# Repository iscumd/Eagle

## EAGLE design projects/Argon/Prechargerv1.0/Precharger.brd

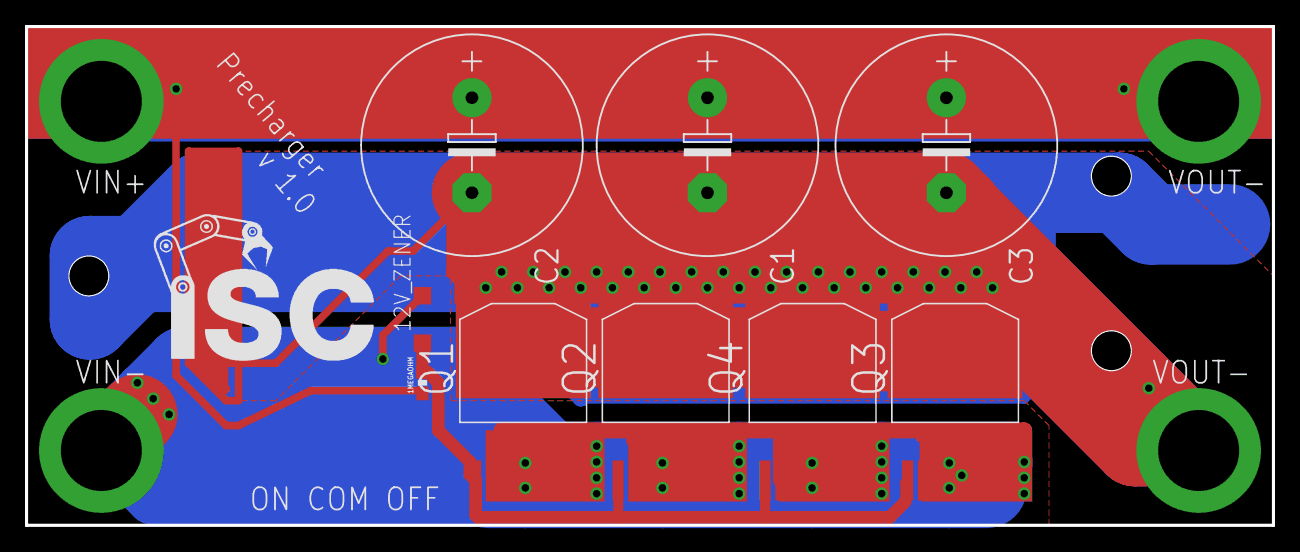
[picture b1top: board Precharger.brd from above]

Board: 2 copper layers, 100.0 x 40.0 mm, 9 parts (0 on the bottom side), 4 nets.

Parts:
1MEGAOHM: 0603-RES
12V_ZENER: SOD123
C1, C2, C3: E7,5-18
Q1, Q2, Q3, Q4: NMOSFET-D2PAK-7; D2PAK-7

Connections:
DRAIN: C1.-, C2.-, C3.-, Q1.D, Q2.D, Q3.D, Q4.D
GATE: 1MEGAOHM.2, 12V_ZENER.C, Q1.G, Q2.G, Q3.G, Q4.G
IN: C1.+, C2.+, C3.+
SOURCE: Q1.S1, Q1.S2, Q1.S3, Q1.S4, Q1.S5, Q2.S1, Q2.S2, Q2.S3, Q2.S4, Q2.S5, Q3.S1, Q3.S2, Q3.S3, Q3.S4, Q3.S5, Q4.S1, Q4.S2, Q4.S3, Q4.S4, Q4.S5

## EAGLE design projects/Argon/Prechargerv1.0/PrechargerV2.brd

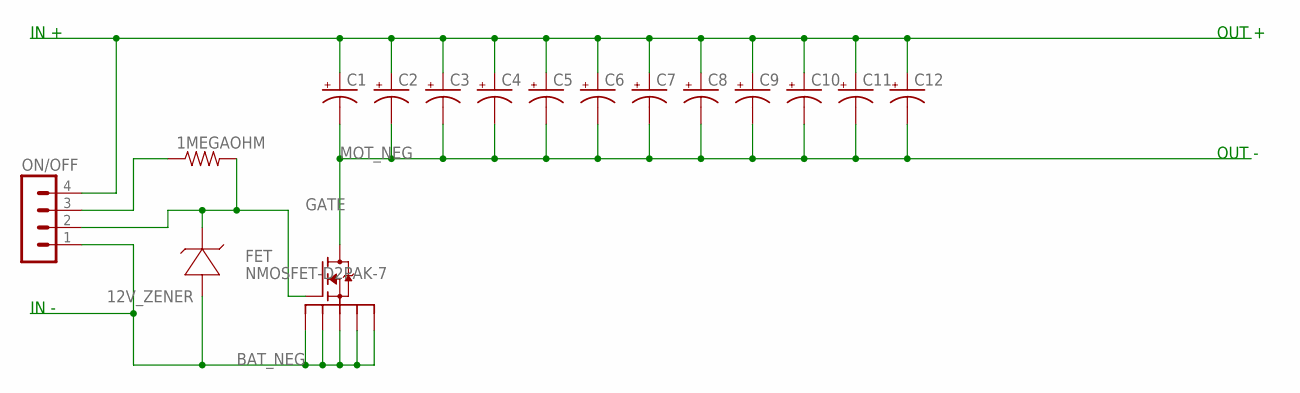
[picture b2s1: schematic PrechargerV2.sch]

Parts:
1MEGAOHM: RESISTOR0603-RES; 0603-RES
12V_ZENER: ZENER; SOD123
C1, C2, C3, C4, C5, C6, C7, C8, C9, C10, C11, C12: CPOL-USE5-13; E5-13
FET: NMOSFET-D2PAK-7; D2PAK-7
ON/OFF: MA04-1

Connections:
BAT_NEG: 12V_ZENER.A (+), FET.S1, FET.S2, FET.S3, FET.S4, FET.S5, ON/OFF.1
BAT_POS: C1.+, C2.+, C3.+, C4.+, C5.+, C6.+, C7.+, C8.+, C9.+, C10.+, C11.+, C12.+
GATE: 1MEGAOHM.2, 12V_ZENER.C (-), FET.G, ON/OFF.2
MOT_NEG: C1.-, C2.-, C3.-, C4.-, C5.-, C6.-, C7.-, C8.-, C9.-, C10.-, C11.-, C12.-, FET.D
unnamed: 1MEGAOHM.1, ON/OFF.3

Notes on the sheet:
OUT -
OUT +
IN -
IN +

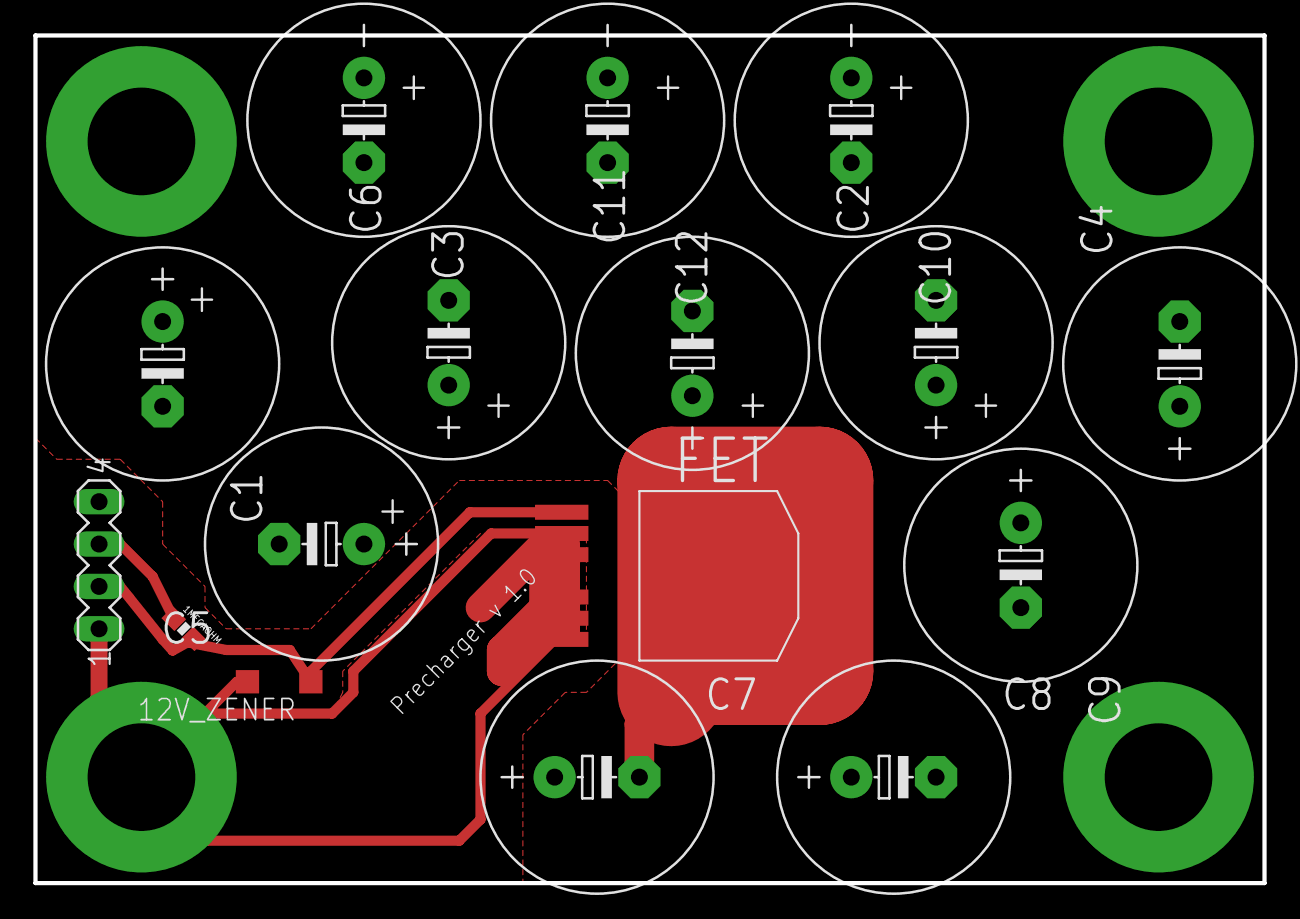
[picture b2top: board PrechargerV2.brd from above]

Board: 2 copper layers, 73.7 x 50.8 mm, 16 parts (0 on the bottom side), 5 nets.

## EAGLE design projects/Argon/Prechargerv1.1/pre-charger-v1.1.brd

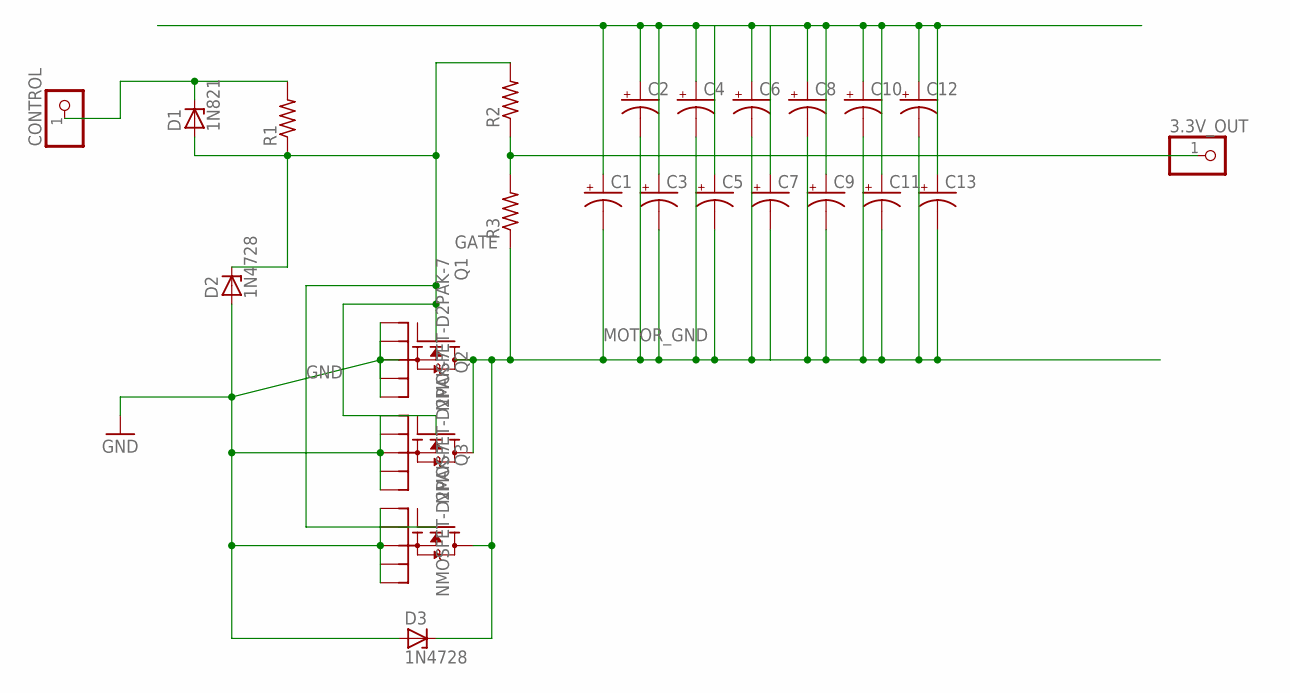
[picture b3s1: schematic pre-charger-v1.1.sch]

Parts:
3.3V_OUT: PINHD-1X1; 1X01
C1, C2, C3, C4, C5, C6, C7, C8, C9, C10, C11, C12, C13: CPOL-USE3.5-8; E3,5-8
CONTROL: PINHD-1X1; 1X01
D1: 1N821; DO35Z10
D2, D3: 1N4728; DO41Z10
Q1, Q2, Q3: NMOSFET-D2PAK-7; D2PAK-7
R1, R2, R3: R-US_0204/7; 0204/7

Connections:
3.3V_OUT: 3.3V_OUT.1, R2.1, R3.2
GATE: D1.A, D2.C, R1.1, R2.2
GND: D2.A, D3.A, Q1.S1, Q1.S2, Q1.S3, Q1.S4, Q1.S5, Q2.S1, Q2.S5, Q3.S1, Q3.S5
MOTOR_GND: C1.-, C2.-, C3.-, C4.-, C5.-, C6.-, C7.-, C8.-, C9.-, C10.-, C11.-, C12.-, C13.-, D3.C, Q1.D, Q2.D, Q3.D, R3.1
unnamed: CONTROL.1, D1.C, R1.2
V_BATT: C1.+, C2.+, C3.+, C4.+, C5.+, C6.+, C7.+, C8.+, C9.+, C10.+, C11.+, C12.+, C13.+

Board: 2 copper layers, 24 parts (0 on the bottom side), 6 nets, no tracks yet.

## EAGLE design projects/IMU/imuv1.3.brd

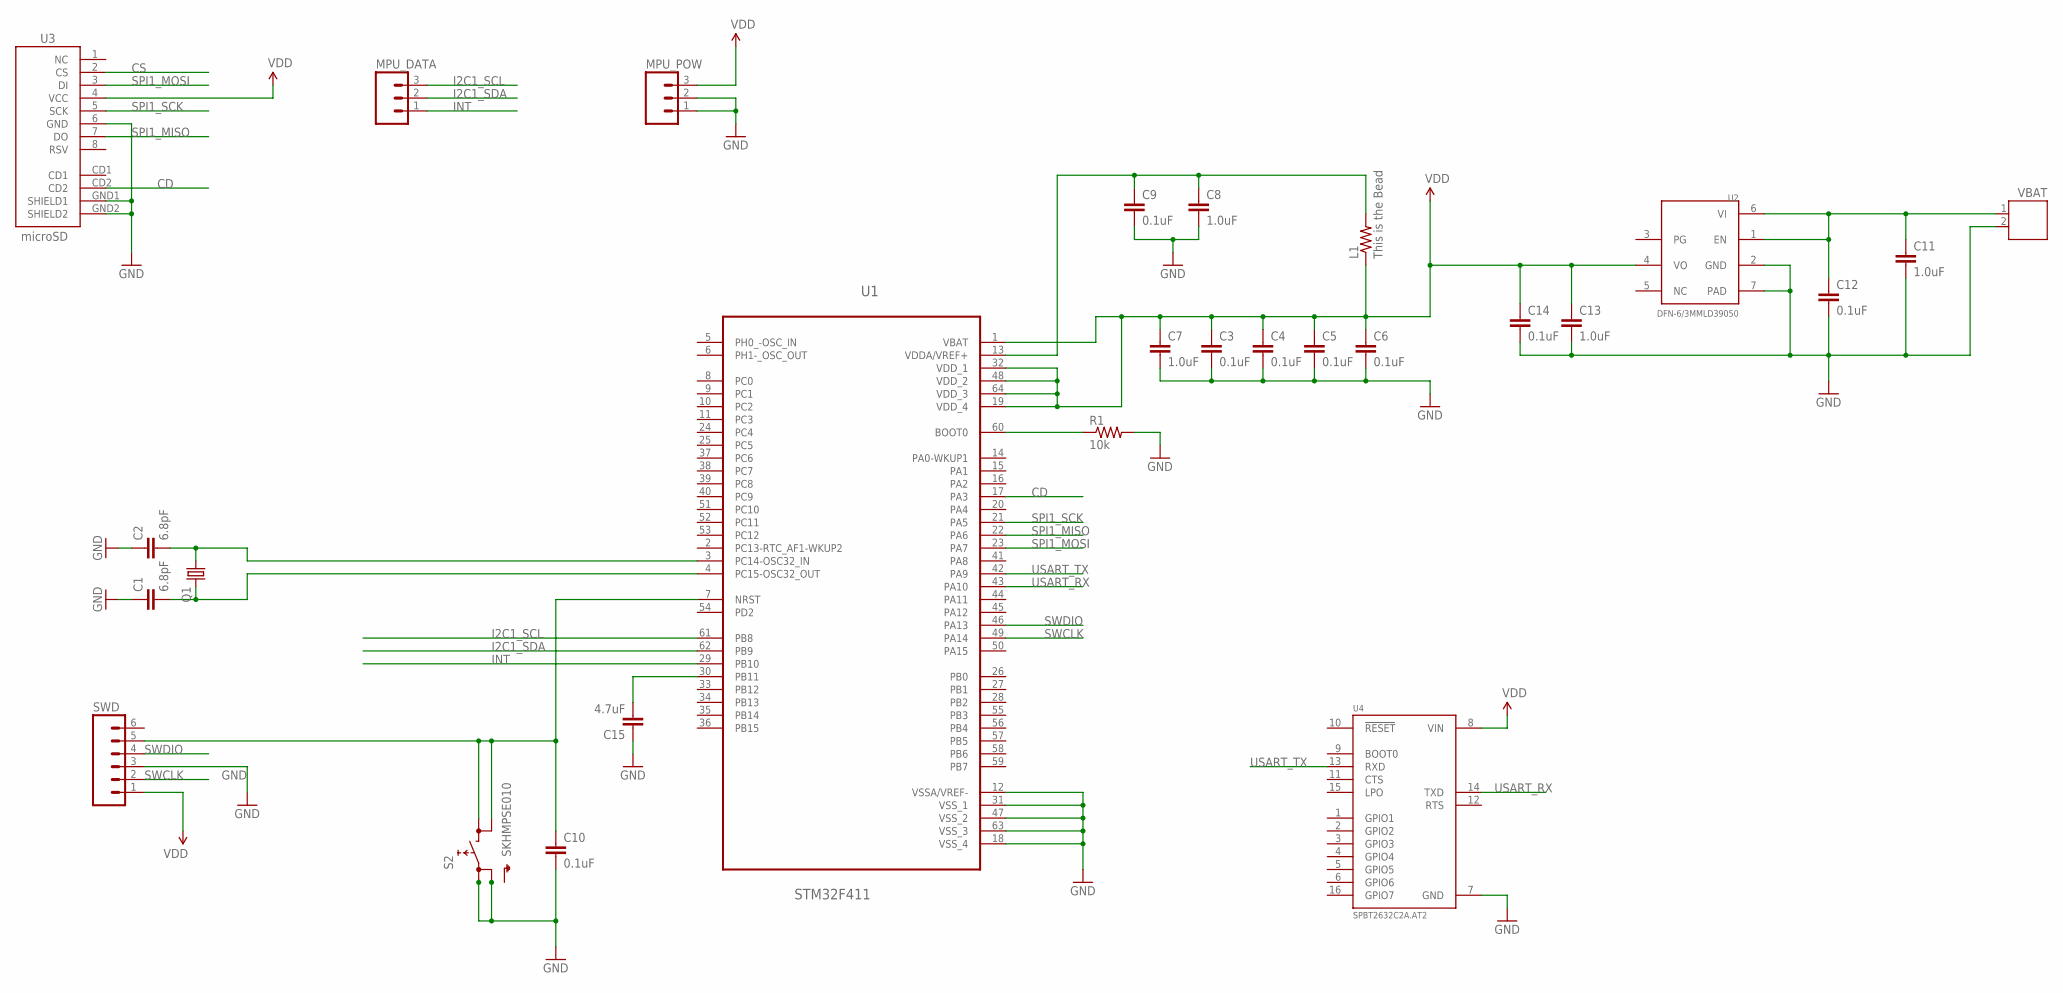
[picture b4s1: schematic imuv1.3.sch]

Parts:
C1, C2: 6.8pF; 0603-CAP
C3, C4, C5, C6, C9, C10, C12, C14: 0.1uF; 0603-CAP
C7, C8, C11, C13: 1.0uF; 0603-CAP
C15: 4.7uF; 1206-CAP
L1: This is the Bead; 0603-RES
MPU_DATA: M03PTH; 1X03
MPU_POW: M03PTH; 1X03
Q1: CRYSTALMM20SS; MM20SS
R1: 10k; 0603-RES
S2: SKHMPSE010; SKHMPXE010
SWD: M06SILK_FEMALE_PTH; 1X06
U1: STM32F411; QFP50P1200X1200X160-64N
U2: DFN-6/3MMLD39050; DFN-6/3MM
U3: microSD; MICRO-SD-SOCKET-PP
U4: SPBT2632C2A.AT2; XCVR_SPBT2632C2A.AT2
VBAT: JST-PH2

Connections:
CD: U1.17 (PA3), U3.CD2
CS: U3.2 (CS)
GND: C1.1, C2.1, C3.2, C4.2, C5.2, C6.2, C7.2, C8.2, C9.2, C10.2, C11.2, C12.2, C13.2, C14.2, C15.1, MPU_POW.1, MPU_POW.2, R1.2, S2.1 (1.1), S2.2 (1.2), SWD.3, U1.12 (VSSA/VREF-), U1.18 (VSS_4), U1.31 (VSS_1), U1.47 (VSS_2), U1.63 (VSS_3), U2.2 (GND), U2.7 (PAD), U3.6 (GND), U3.GND1 (SHIELD1), U3.GND2 (SHIELD2), U4.7 (GND), VBAT.2
I2C1_SCL: MPU_DATA.3, U1.61 (PB8)
I2C1_SDA: MPU_DATA.2, U1.62 (PB9)
INT: MPU_DATA.1, U1.29 (PB10)
unnamed: C1.2, Q1.4 (2), U1.4 (PC15-OSC32_OUT)
unnamed: C10.1, S2.3 (2.1), S2.4 (2.2), SWD.5, U1.7 (NRST)
unnamed: R1.1, U1.60 (BOOT0)
unnamed: C8.1, C9.1, L1.2, U1.13 (VDDA/VREF+)
unnamed: C2.2, Q1.1, U1.3 (PC14-OSC32_IN)
unnamed: C11.1, C12.1, U2.1 (EN), U2.6 (VI), VBAT.1
unnamed: C15.2, U1.30 (PB11)
NC: U2.5 (NC)
PG: U2.3 (PG)
SPI1_MISO: U1.22 (PA6), U3.7 (DO)
SPI1_MOSI: U1.23 (PA7), U3.3 (DI)
SPI1_SCK: U1.21 (PA5), U3.5 (SCK)
SWCLK: SWD.2, U1.49 (PA14)
SWDIO: SWD.4, U1.46 (PA13)
USART_RX: U1.43 (PA10), U4.14 (TXD)
USART_TX: U1.42 (PA9), U4.13 (RXD)
VDD: C3.1, C4.1, C5.1, C6.1, C7.1, C13.1, C14.1, L1.1, MPU_POW.3, SWD.1, U1.1 (VBAT), U1.19 (VDD_4), U1.32 (VDD_1), U1.48 (VDD_2), U1.64 (VDD_3), U2.4 (VO), U3.4 (VCC), U4.8 (VIN)

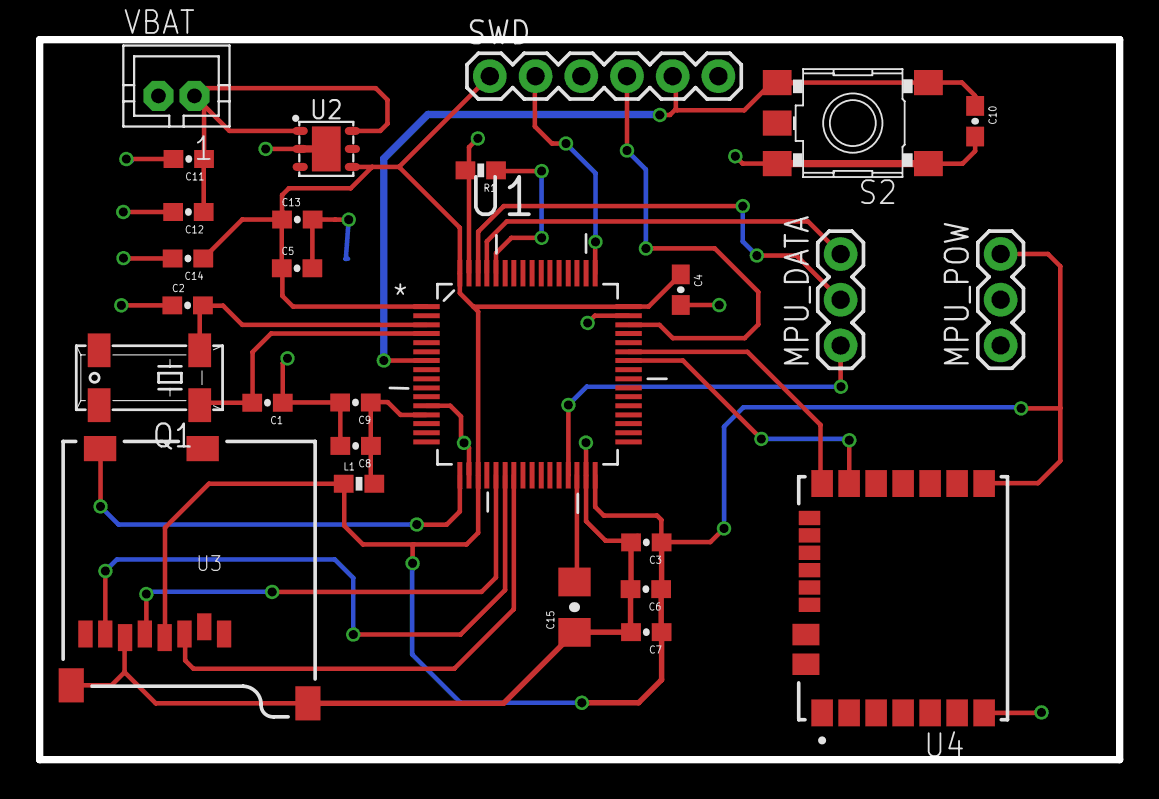
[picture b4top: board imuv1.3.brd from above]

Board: 2 copper layers, 60.0 x 40.0 mm, 27 parts (0 on the bottom side), 20 nets.

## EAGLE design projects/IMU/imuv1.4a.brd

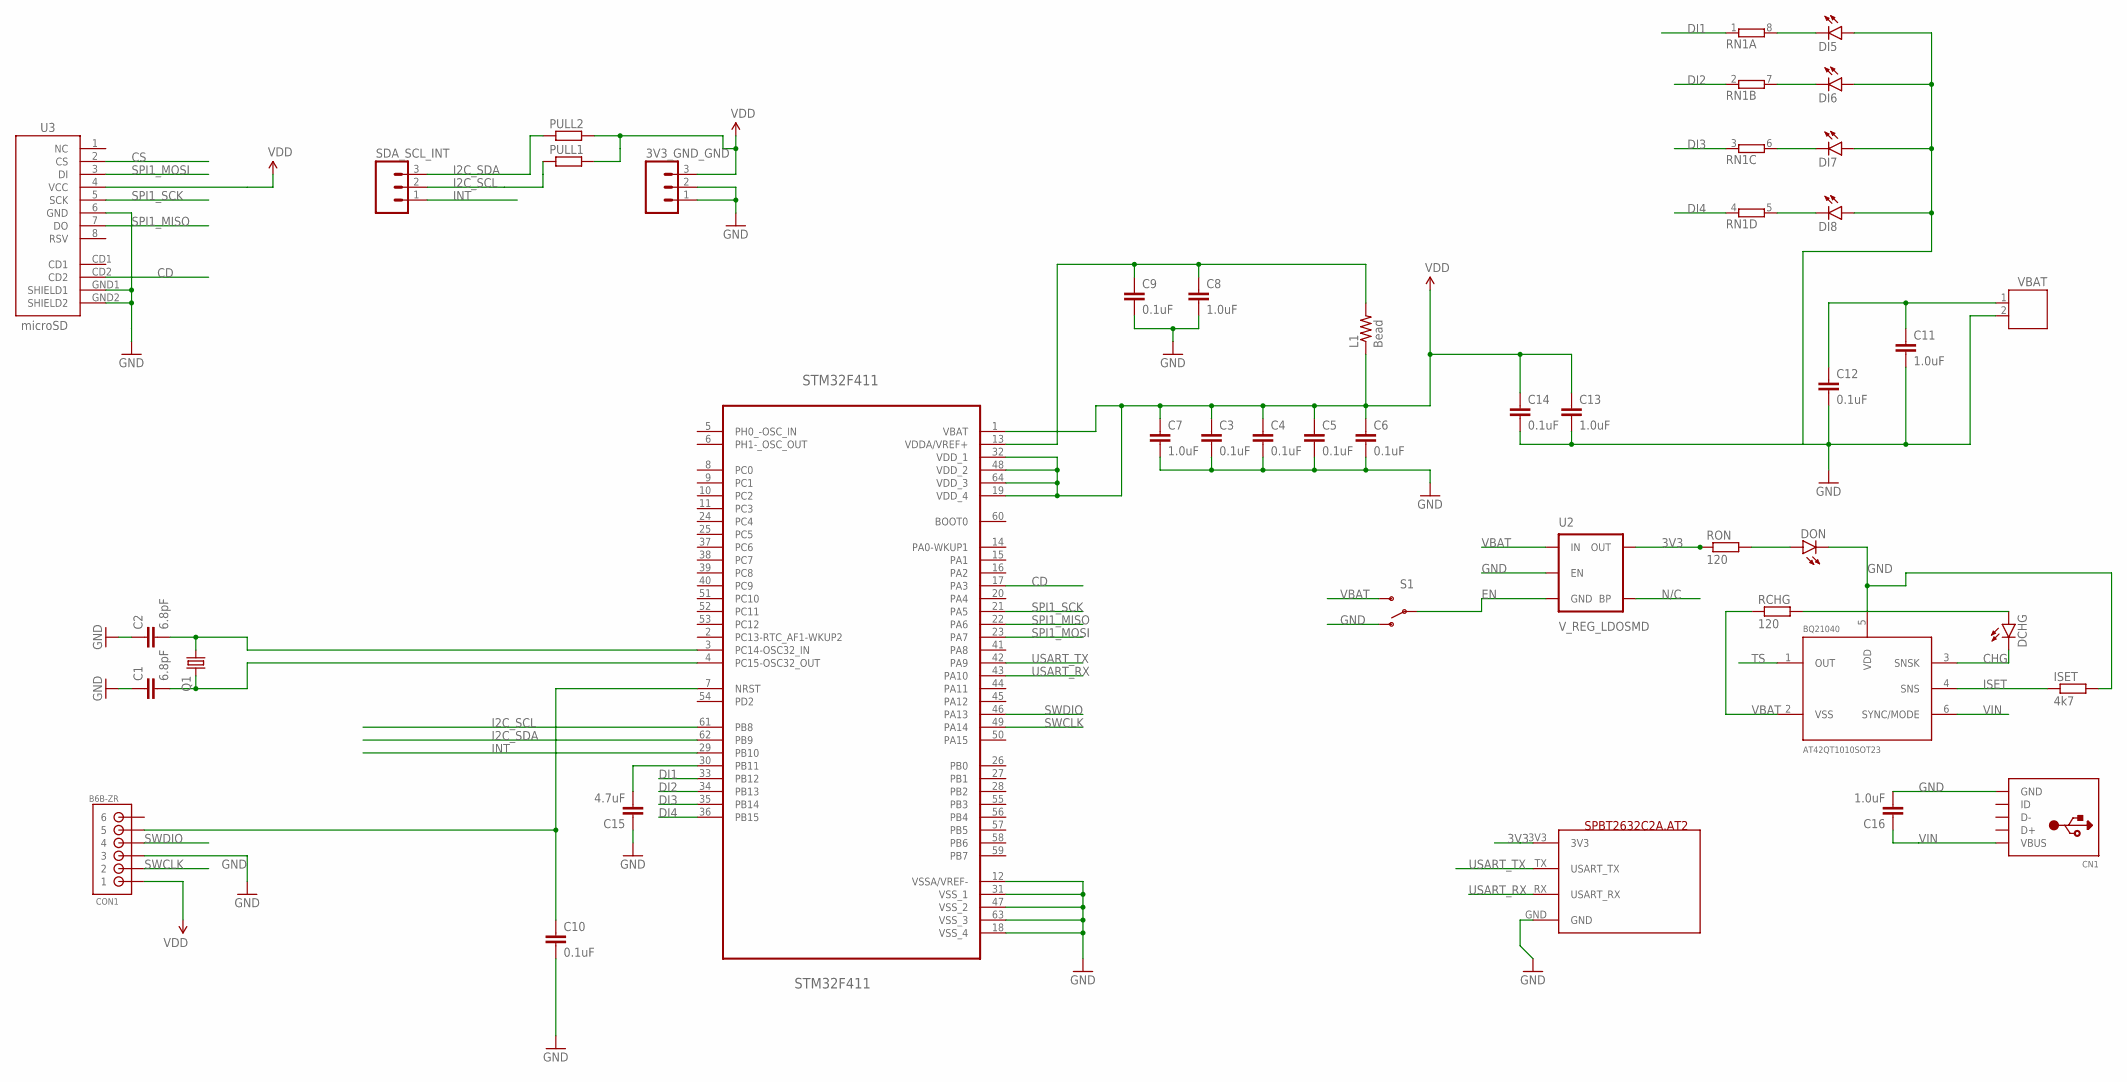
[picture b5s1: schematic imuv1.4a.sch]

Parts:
3V3_GND_GND: M03PTH; 1X03
BQ21040: AT42QT1010SOT23; SOT23-6
C1, C2: 6.8pF; 0603-CAP
C3, C4, C5, C6, C9, C10, C12, C14: 0.1uF; 0603-CAP
C7, C8, C11, C13, C16: 1.0uF; 0603-CAP
C15: 4.7uF; 1206-CAP
CN1: USBMINIB; USB-MINIB
CON1: B6B-ZR
DCHG: LED0603; LED-0603
DI5, DI6, DI7, DI8: LED0603; LED-0603
DON: LED0603; LED-0603
ISET: 4k7; R0603
L1: Bead; 0603-RES
PULL1, PULL2: R-EU_R0603; R0603
Q1: CRYSTALMM20SS; MM20SS
RCHG: 120; R0603
RN1: 4R-N0603-ARV; 0603-ARV
RON: 120; R0603
S1: SWITCH-SPDTPTH; SWITCH-SPDT
SDA_SCL_INT: M03PTH; 1X03
STM32F411: STM32F411; QFP50P1200X1200X160-64N
U2: V_REG_LDOSMD; SOT23-5
U3: microSD; MICRO-SD-SOCKET-PP
U$1: BT; SPBT2632C2A.AT2_XCVR_SPBT2632C2A.AT2
VBAT: JST-PH2

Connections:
3V3: 3V3_GND_GND.3, C3.1, C4.1, C5.1, C6.1, C7.1, C13.1, C14.1, C15.2, CON1.1, L1.1, PULL1.2, PULL2.2, RON.1, STM32F411.1 (VBAT), STM32F411.19 (VDD_4), STM32F411.30 (PB11), STM32F411.32 (VDD_1), STM32F411.48 (VDD_2), STM32F411.64 (VDD_3), U2.5 (OUT), U3.4 (VCC), U$1.3V3
AREF: C8.1, C9.1, L1.2, STM32F411.13 (VDDA/VREF+)
CD: STM32F411.17 (PA3), U3.CD2
CHG: BQ21040.3 (SNSK), DCHG.C
CS: U3.2 (CS)
DI1: RN1.1, STM32F411.33 (PB12)
DI2: RN1.2 (1), STM32F411.34 (PB13)
DI3: RN1.3 (1), STM32F411.35 (PB14)
DI4: RN1.4 (1), STM32F411.36 (PB15)
EN: S1.2, U2.2 (GND)
GND: 3V3_GND_GND.1, 3V3_GND_GND.2, BQ21040.5 (VDD), C1.1, C2.1, C3.2, C4.2, C5.2, C6.2, C7.2, C8.2, C9.2, C10.2, C11.2, C12.2, C13.2, C14.2, C15.1, C16.2, CN1.GND, CON1.3, DI5.A, DI6.A, DI7.A, DI8.A, DON.C, ISET.2, S1.1 (O), STM32F411.12 (VSSA/VREF-), STM32F411.18 (VSS_4), STM32F411.31 (VSS_1), STM32F411.47 (VSS_2), STM32F411.63 (VSS_3), U2.3 (EN), U3.6 (GND), U3.GND1 (SHIELD1), U3.GND2 (SHIELD2), U$1.GND, VBAT.2
I2C_SCL: PULL1.1, SDA_SCL_INT.2, STM32F411.61 (PB8)
I2C_SDA: PULL2.1, SDA_SCL_INT.3, STM32F411.62 (PB9)
INT: SDA_SCL_INT.1, STM32F411.29 (PB10)
ISET: BQ21040.4 (SNS), ISET.1
unnamed: C1.2, Q1.4 (2), STM32F411.4 (PC15-OSC32_OUT)
unnamed: DON.A, RON.2
unnamed: DI5.C, RN1.8 (2)
unnamed: C2.2, Q1.1, STM32F411.3 (PC14-OSC32_IN)
unnamed: DI6.C, RN1.7 (2)
unnamed: DI7.C, RN1.6 (2)
unnamed: DI8.C, RN1.5 (2)
N/C: U2.4 (BP)
OUT: DCHG.A, RCHG.2
RST: C10.1, CON1.5, STM32F411.7 (NRST)
SPI1_MISO: STM32F411.22 (PA6), U3.7 (DO)
SPI1_MOSI: STM32F411.23 (PA7), U3.3 (DI)
SPI1_SCK: STM32F411.21 (PA5), U3.5 (SCK)
SWCLK: CON1.2, STM32F411.49 (PA14)
SWDIO: CON1.4, STM32F411.46 (PA13)
TS: BQ21040.1 (OUT)
USART_RX: STM32F411.43 (PA10), U$1.RX (USART_RX)
USART_TX: STM32F411.42 (PA9), U$1.TX (USART_TX)
VBAT: BQ21040.2 (VSS), C11.1, C12.1, RCHG.1, S1.3 (S), U2.1 (IN), VBAT.1
VIN: BQ21040.6 (SYNC/MODE), C16.1, CN1.VBUS

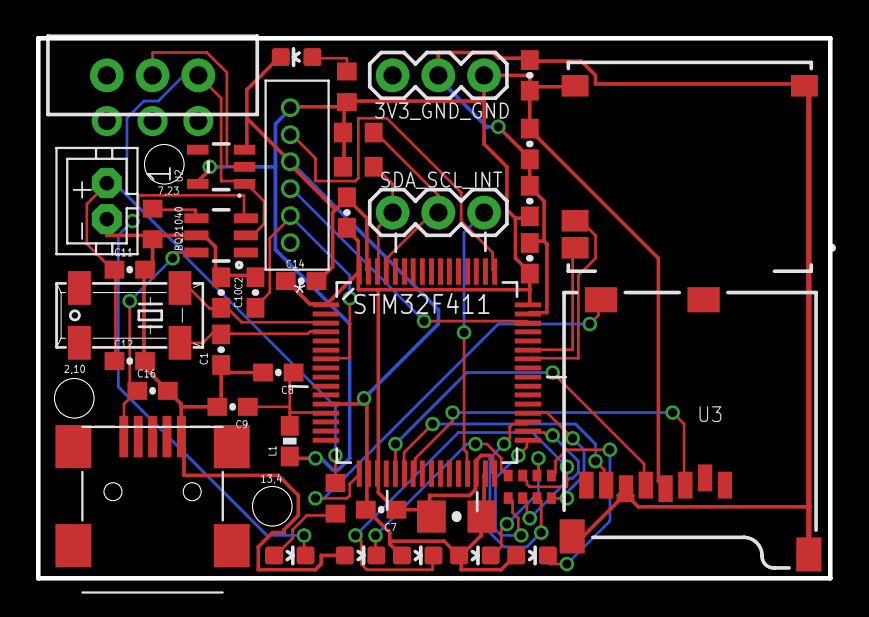
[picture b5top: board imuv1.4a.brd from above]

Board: 2 copper layers, 44.0 x 30.0 mm, 41 parts (0 on the bottom side), 32 nets.

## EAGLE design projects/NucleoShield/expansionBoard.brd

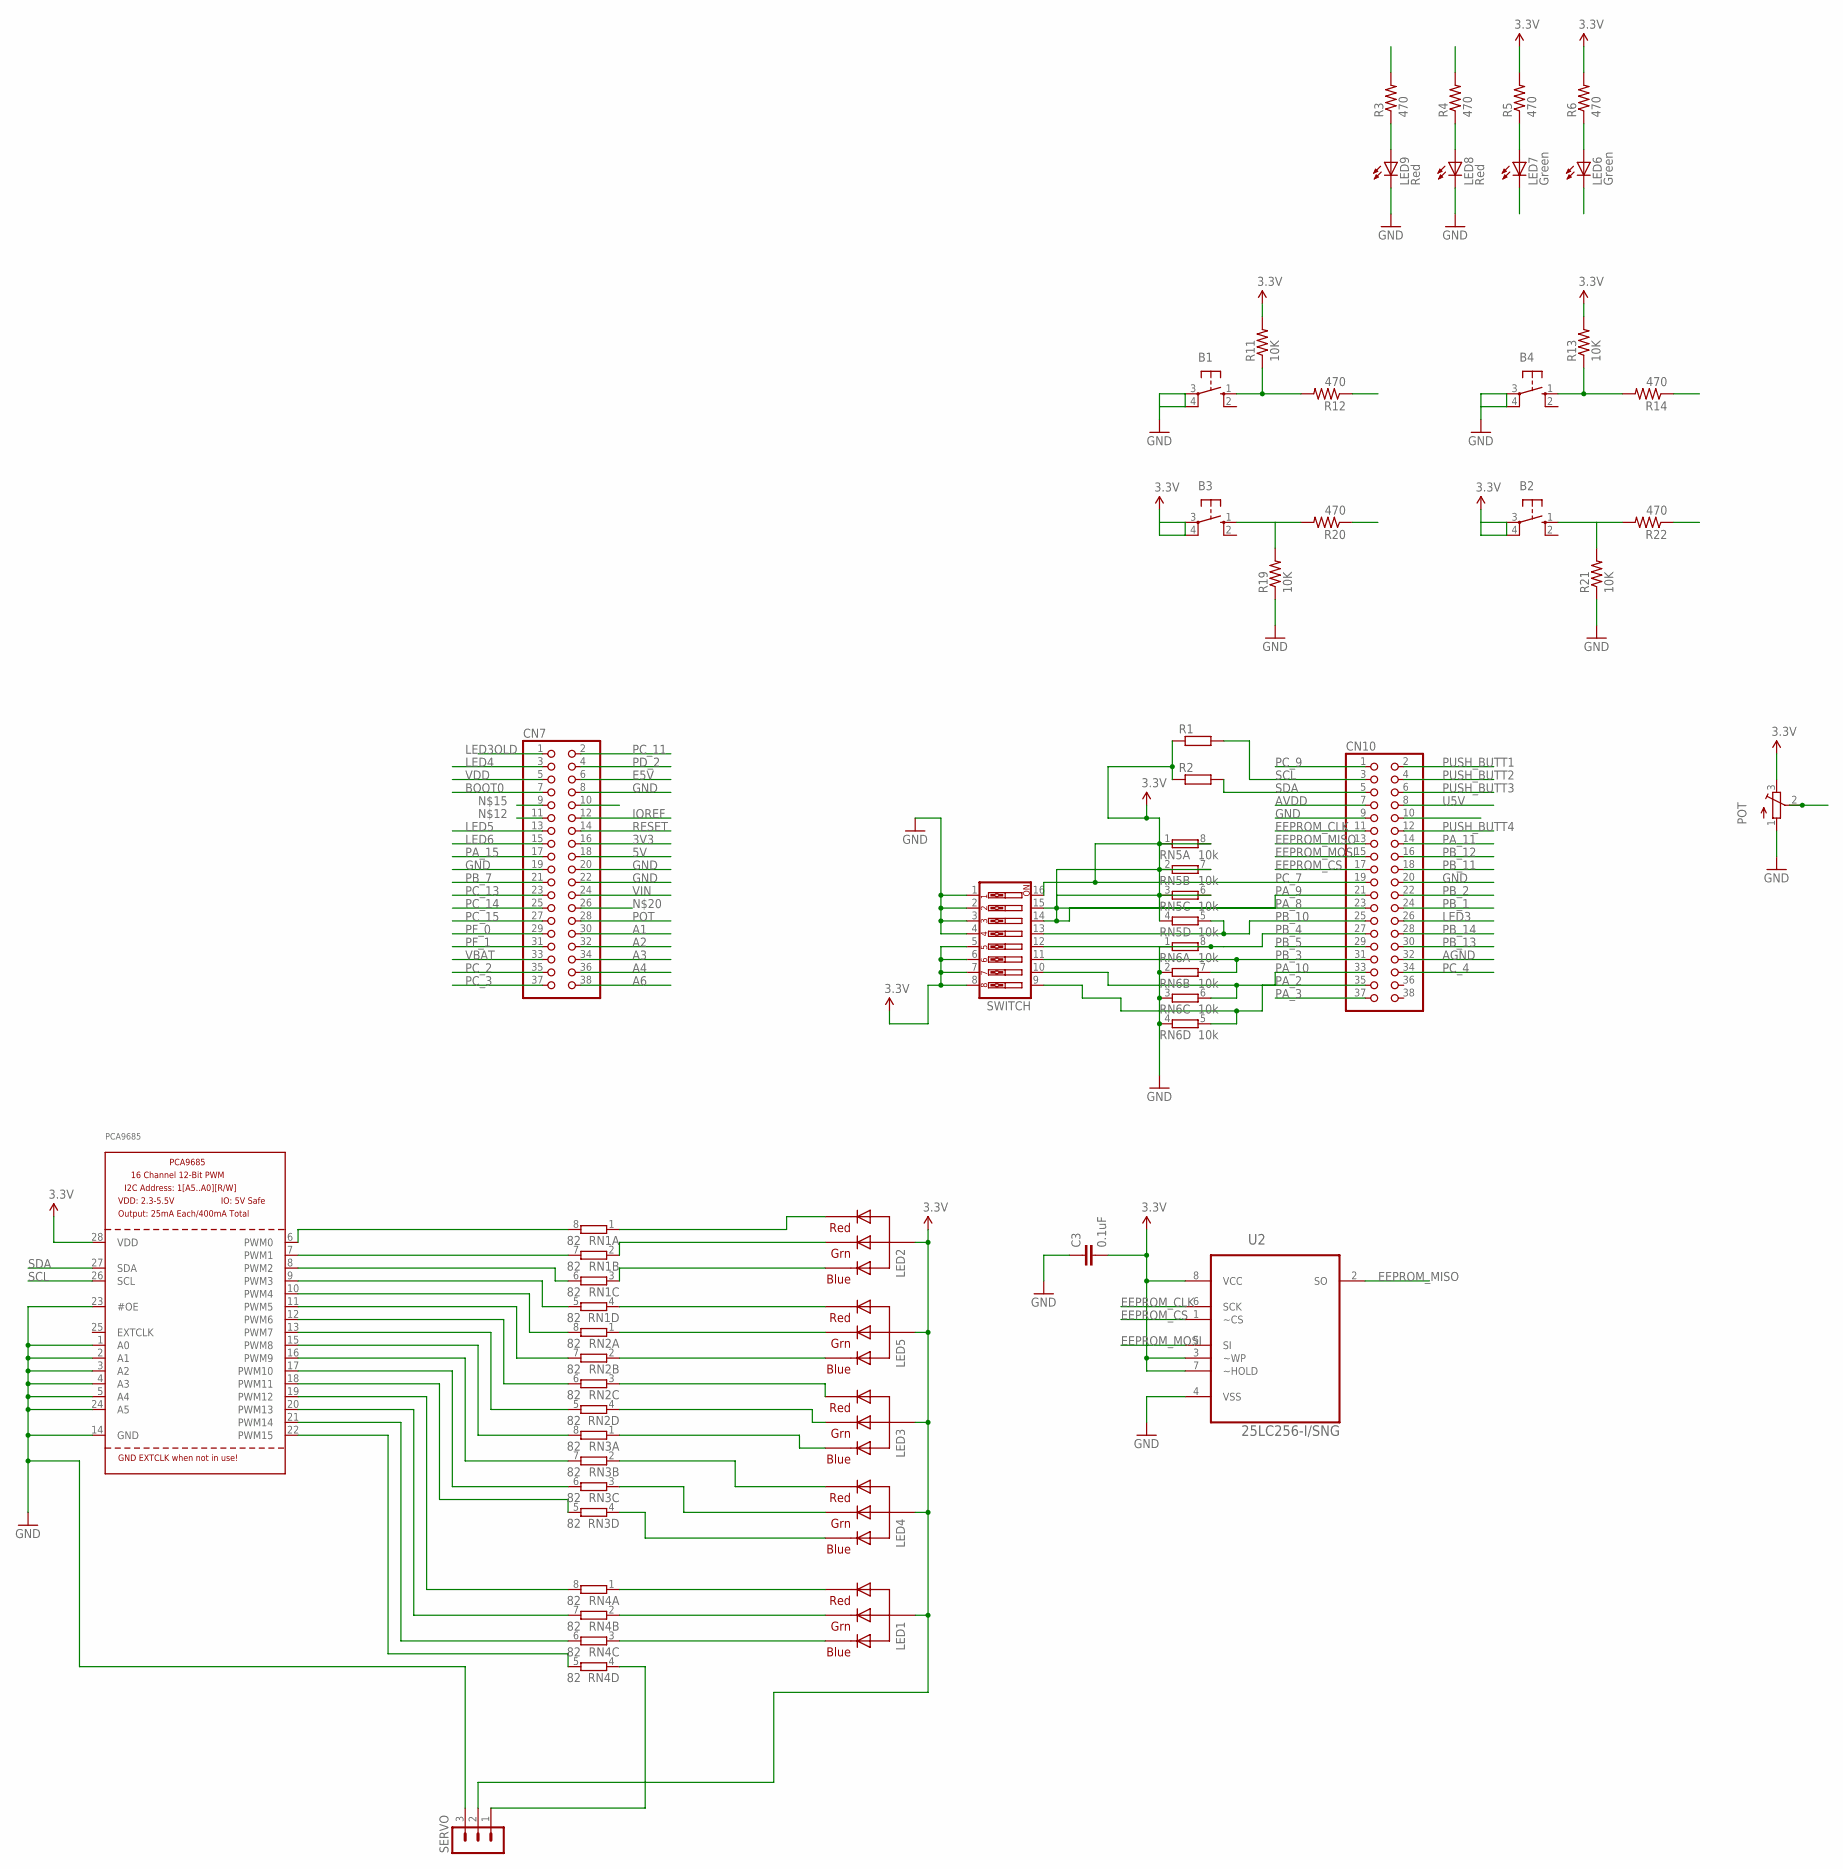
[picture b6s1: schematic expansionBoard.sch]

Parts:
B1, B2, B3, B4: 10-XX; B3F-10XX
C3: 0.1uF; 0402-CAP
CN7, CN10: PINHD-2X19; 2X19
LED1, LED2, LED3, LED4, LED5: RGBLED_CA-5MM; LED5MMRGB
LED6, LED7: Green; LED-0603
LED8, LED9: Red; LED-0603
PCA9685: PCA9685; TSSOP28
POT: TRIMPOT3386; TRIM-3386
R1, R2: RR0603; R0603
R3, R4, R5, R6, R12, R14, R20, R22: 470; 0402-RES
R11, R13, R19, R21: 10K; 0402-RES
RN1, RN2, RN3, RN4: 82; 0603-ARC
RN5, RN6: 10k; 0603-ARC
SERVO: MA03-1
SWITCH: SW_DIP-8; EDG-08
U2: 25LC256-I/SNG; SOIC127P600X175-8N

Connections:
3V3: CN7.16
5V: CN7.18
A1: CN7.30
A2: CN7.32
A3: CN7.34
A4: CN7.36
A6: CN7.38
AGND: CN10.32
AVDD: CN10.7
BOOT0: CN7.7
E5V: CN7.6
EEPROM_CLK: CN10.11, U2.6 (SCK)
EEPROM_CS: CN10.17, U2.1 (~CS)
EEPROM_MISO: CN10.13, U2.2 (SO)
EEPROM_MOSI: CN10.15, U2.5 (SI)
GND: B1.3, B1.4 (P1), B4.3, B4.4 (P1), C3.1, CN7.8, CN7.19, CN7.20, CN7.22, CN10.9, CN10.20, LED8.C, LED9.C, PCA9685.1 (A0), PCA9685.2 (A1), PCA9685.3 (A2), PCA9685.4 (A3), PCA9685.5 (A4), PCA9685.14 (GND), PCA9685.23 (#OE), PCA9685.24 (A5), POT.1 (A), R19.1, R21.1, RN6.1, RN6.2 (1), RN6.3 (1), RN6.4 (1), SERVO.3, SWITCH.1, SWITCH.2, SWITCH.3, SWITCH.4, U2.4 (VSS)
IOREF: CN7.12
LED3: CN10.26, R3.2
LED3OLD: CN7.1
LED4: CN7.3, R4.2
LED5: CN7.13, LED7.C
LED6: CN7.15, LED6.C
unnamed: PCA9685.6 (PWM0), RN1.8 (2)
unnamed: PCA9685.7 (PWM1), RN1.7 (2)
unnamed: LED9.A, R3.1
unnamed: LED8.A, R4.1
unnamed: LED2.1 (RED), RN1.1
unnamed: PCA9685.8 (PWM2), RN1.6 (2)
unnamed: LED7.A, R5.1
unnamed: LED6.A, R6.1
unnamed: LED2.4 (BLUE), RN1.3 (1)
unnamed: PCA9685.9 (PWM3), RN1.5 (2)
unnamed: PCA9685.10 (PWM4), RN2.8 (2)
unnamed: PCA9685.11 (PWM5), RN2.7 (2)
unnamed: PCA9685.12 (PWM6), RN2.6 (2)
unnamed: PCA9685.13 (PWM7), RN2.5 (2)
unnamed: PCA9685.15 (PWM8), RN3.8 (2)
unnamed: PCA9685.16 (PWM9), RN3.7 (2)
unnamed: PCA9685.17 (PWM10), RN3.6 (2)
unnamed: PCA9685.18 (PWM11), RN3.5 (2)
unnamed: B4.1 (S), R13.1, R14.2
unnamed: B1.1 (S), R11.1, R12.2
unnamed: PCA9685.19 (PWM12), RN4.8 (2)
unnamed: PCA9685.20 (PWM13), RN4.7 (2)
unnamed: PCA9685.21 (PWM14), RN4.6 (2)
unnamed: LED2.3 (GREEN), RN1.2 (1)
unnamed: B3.1 (S), R19.2, R20.2
unnamed: B2.1 (S), R21.2, R22.2
unnamed: PCA9685.22 (PWM15), RN4.5 (2)
unnamed: RN4.4 (1), SERVO.1
unnamed: LED1.4 (BLUE), RN4.3 (1)
unnamed: LED1.3 (GREEN), RN4.2 (1)
unnamed: LED1.1 (RED), RN4.1
unnamed: LED5.1 (RED), RN1.4 (1)
unnamed: LED5.3 (GREEN), RN2.1
unnamed: LED5.4 (BLUE), RN2.2 (1)
unnamed: LED3.1 (RED), RN2.3 (1)
unnamed: LED3.3 (GREEN), RN2.4 (1)
unnamed: LED3.4 (BLUE), RN3.1
unnamed: LED4.1 (RED), RN3.2 (1)
unnamed: LED4.3 (GREEN), RN3.3 (1)
unnamed: LED4.4 (BLUE), RN3.4 (1)
PA_2: CN10.35, RN6.5 (2), SWITCH.9
PA_3: CN10.37
PA_8: CN10.23, RN5.6 (2), SWITCH.14
PA_9: CN10.21, RN5.7 (2), SWITCH.15
PA_10: CN10.33, RN6.6 (2), SWITCH.10
PA_11: CN10.14
PA_15: CN7.17
PB_1: CN10.24
PB_2: CN10.22
PB_3: CN10.31, RN6.7 (2), SWITCH.11
PB_4: CN10.27, RN6.8 (2), SWITCH.12
PB_5: CN10.29
PB_7: CN7.21
PB_10: CN10.25, RN5.5 (2), SWITCH.13
PB_11: CN10.18
PB_12: CN10.16
PB_13: CN10.30
PB_14: CN10.28
PC_2: CN7.35
PC_3: CN7.37
PC_4: CN10.34
PC_7: CN10.19, RN5.8 (2), SWITCH.16
PC_9: CN10.1
PC_11: CN7.2
PC_13: CN7.23
PC_14: CN7.25
PC_15: CN7.27
PD_2: CN7.4
PF_0: CN7.29
PF_1: CN7.31
POT: CN7.28, POT.2 (S)
PUSH_BUTT1: CN10.2
PUSH_BUTT2: CN10.4
PUSH_BUTT3: CN10.6
PUSH_BUTT4: CN10.12
RESET: CN7.14
SCL: CN10.3, PCA9685.26 (SCL), R1.2
SDA: CN10.5, PCA9685.27 (SDA), R2.2
U5V: CN10.8
VBAT: CN7.33
VCC: B2.3, B2.4 (P1), B3.3, B3.4 (P1), C3.2, LED1.2 (VCC), LED2.2 (VCC), LED3.2 (VCC), LED4.2 (VCC), LED5.2 (VCC), PCA9685.28 (VDD), POT.3 (E), R1.1, R2.1, R5.2, R6.2, R11.2, R13.2, RN5.1, RN5.2 (1), RN5.3 (1), RN5.4 (1), SERVO.2, SWITCH.5, SWITCH.6, SWITCH.7, SWITCH.8, U2.3 (~WP), U2.7 (~HOLD), U2.8 (VCC)
VDD: CN7.5
VIN: CN7.24

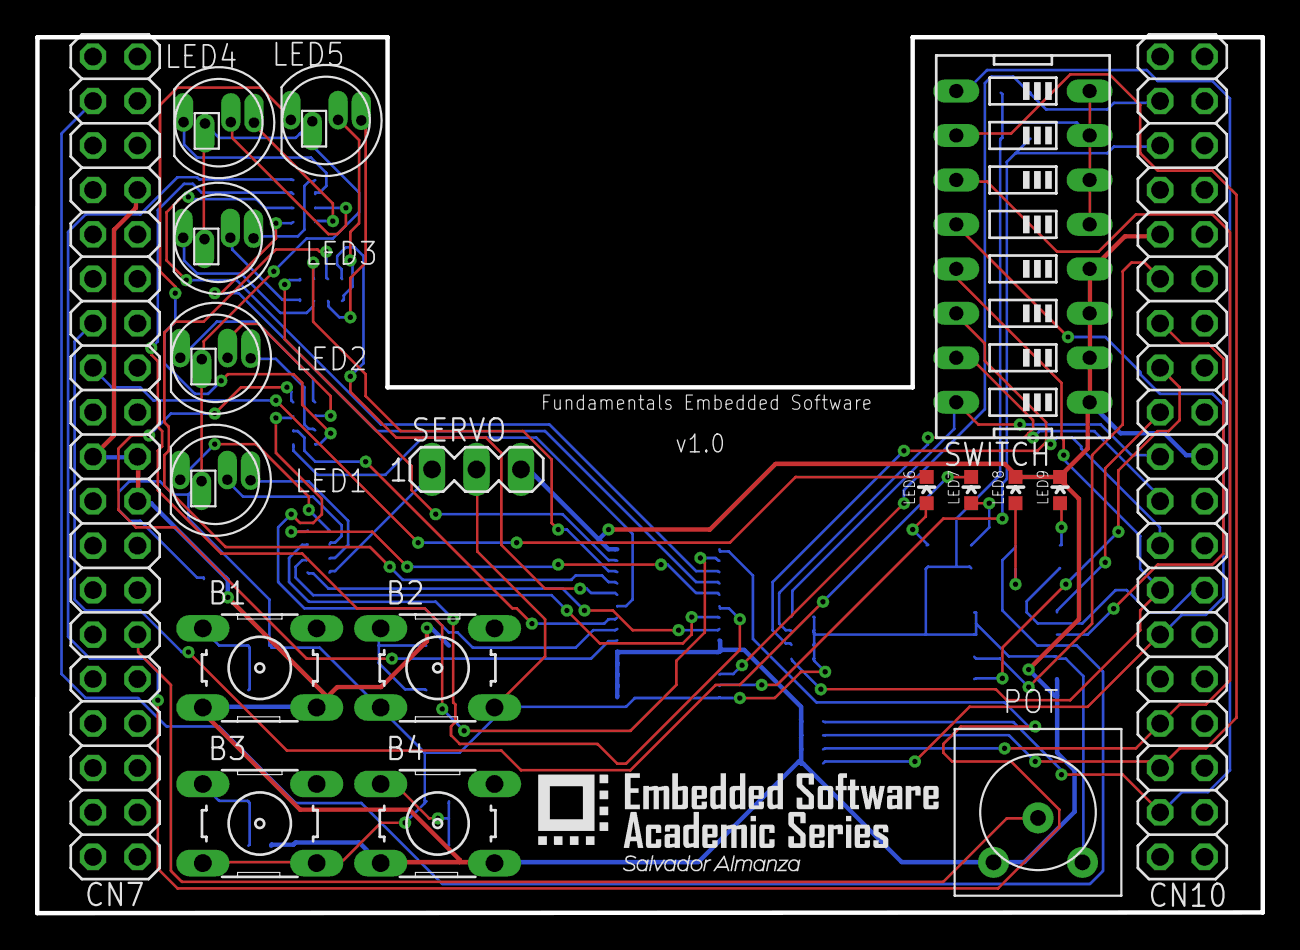
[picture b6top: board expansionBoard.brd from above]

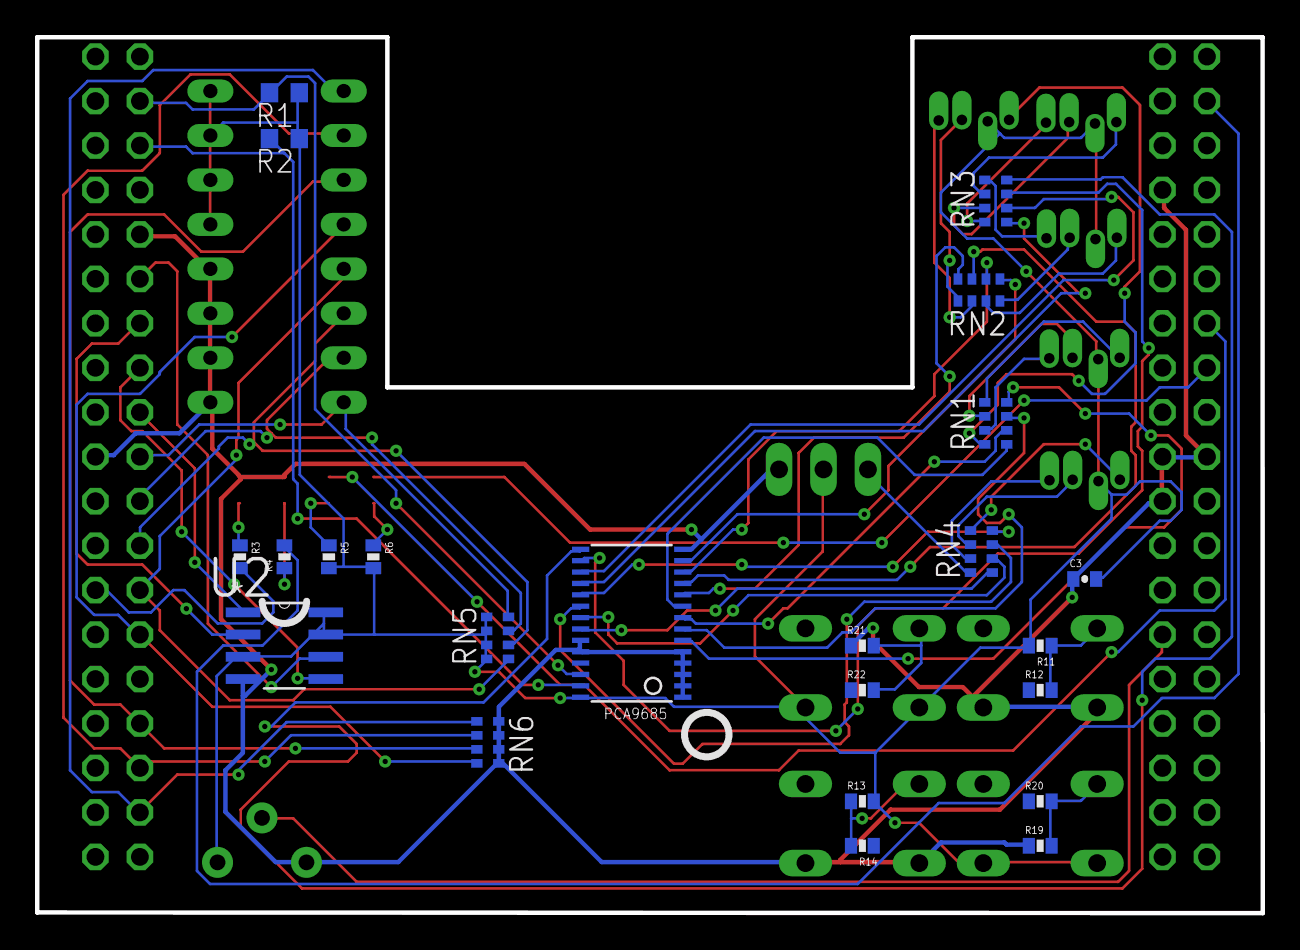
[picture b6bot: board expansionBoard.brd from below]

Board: 2 copper layers, 70.0 x 50.0 mm, 41 parts (23 on the bottom side), 61 nets.

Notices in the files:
parts and their libraries:
SparkFun-DiscreteSemi: Licensing: Creative Commons ShareAlike 4.0 International - https://creativecommons.org/licenses/by-sa/4.0
